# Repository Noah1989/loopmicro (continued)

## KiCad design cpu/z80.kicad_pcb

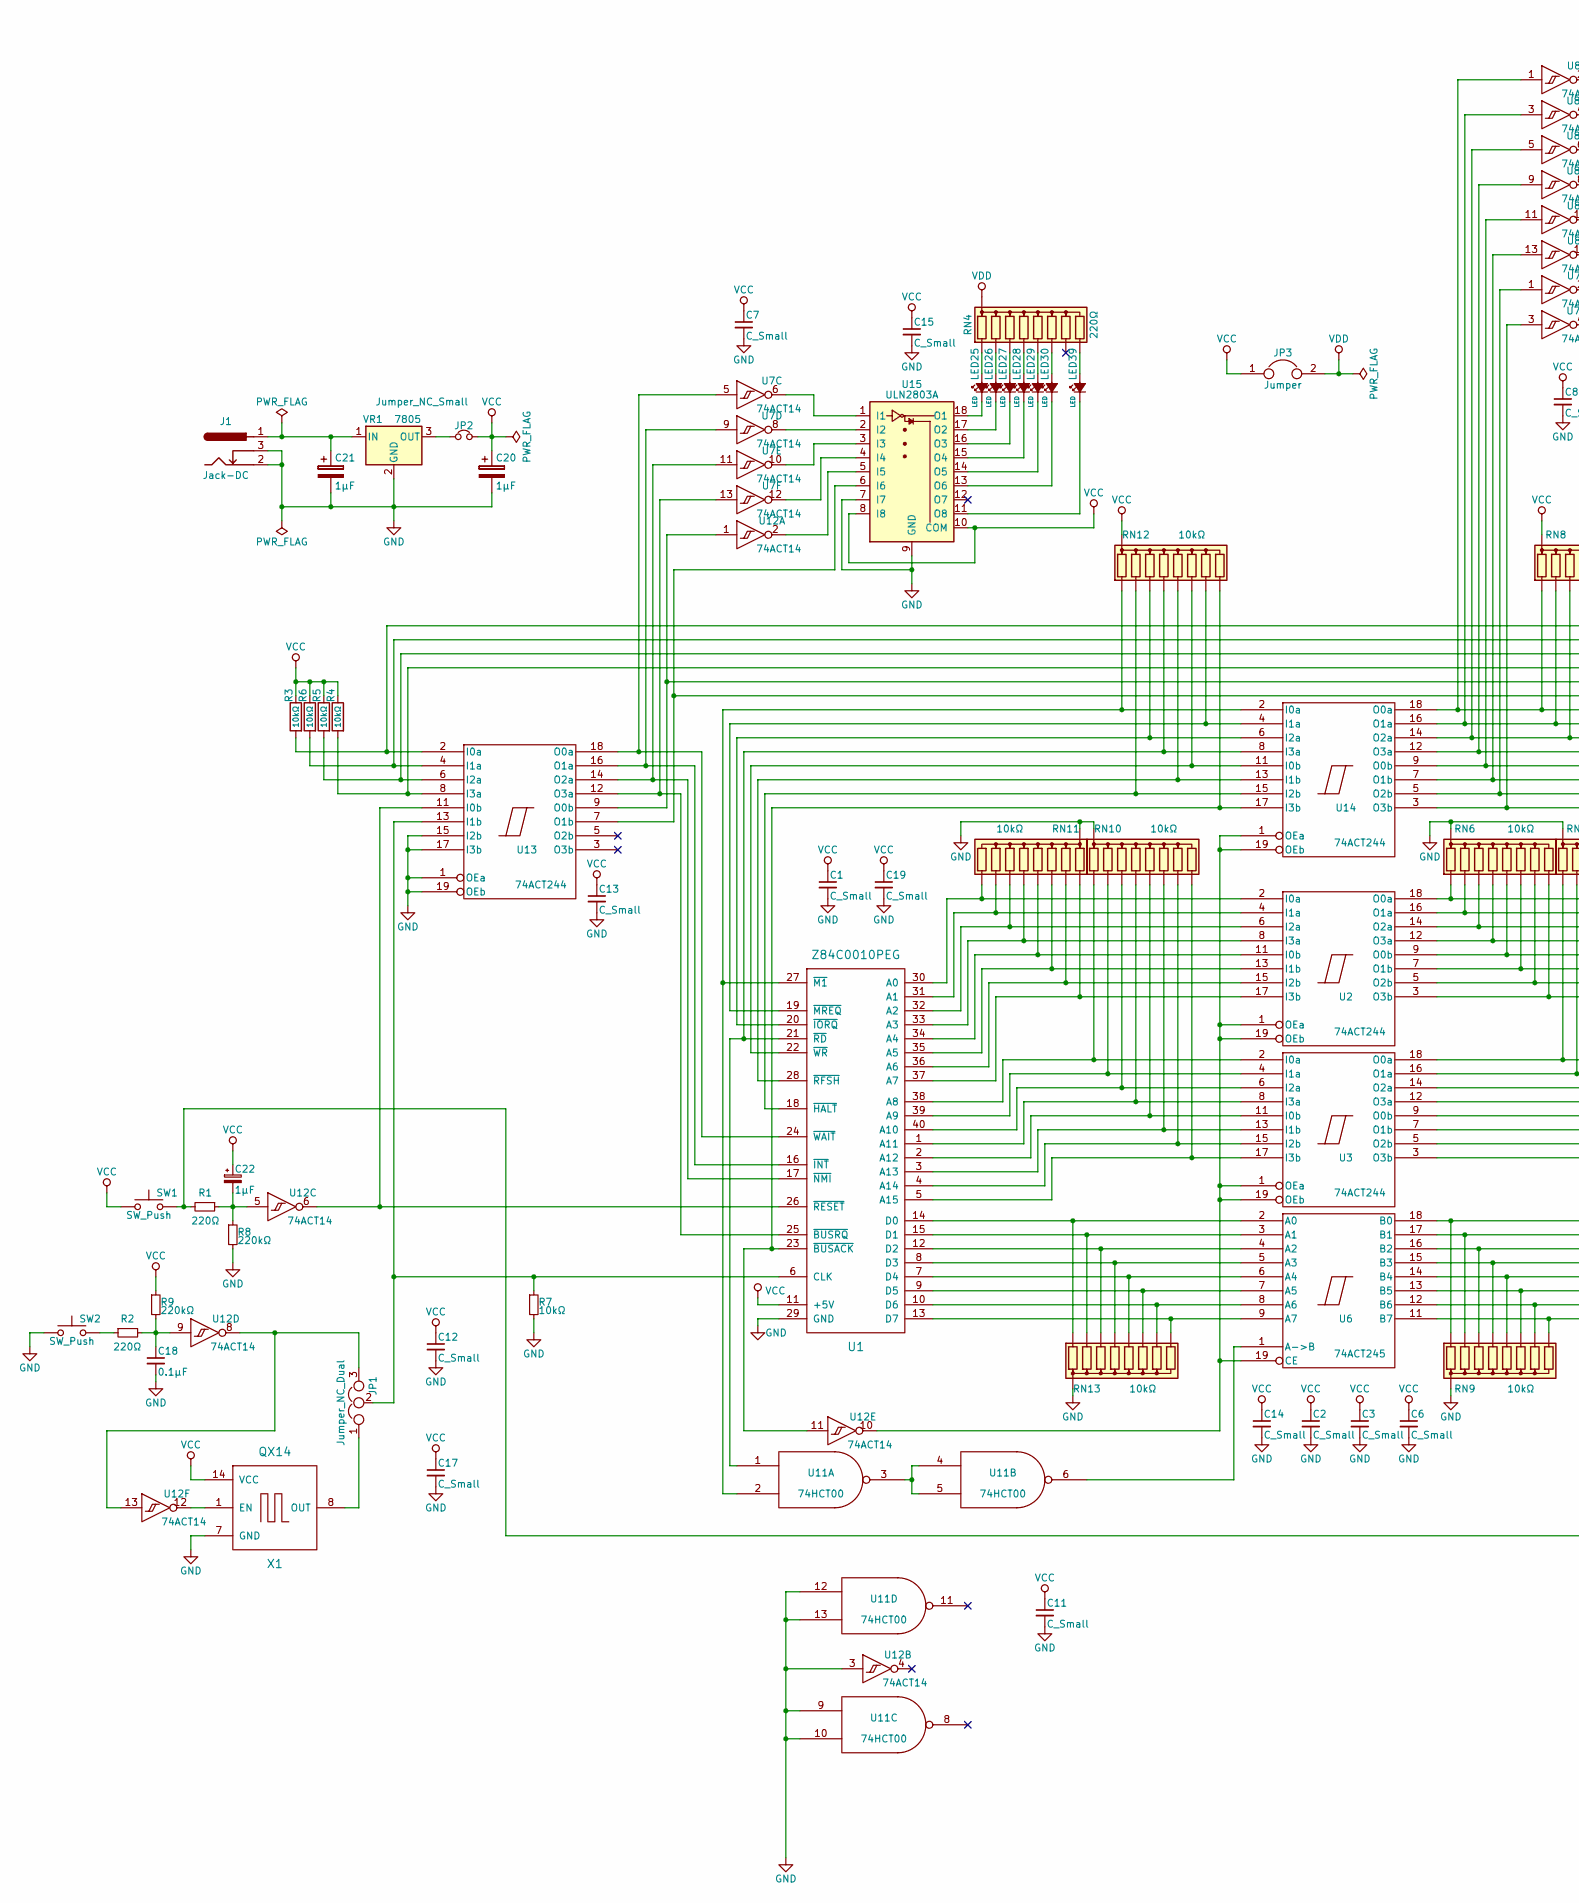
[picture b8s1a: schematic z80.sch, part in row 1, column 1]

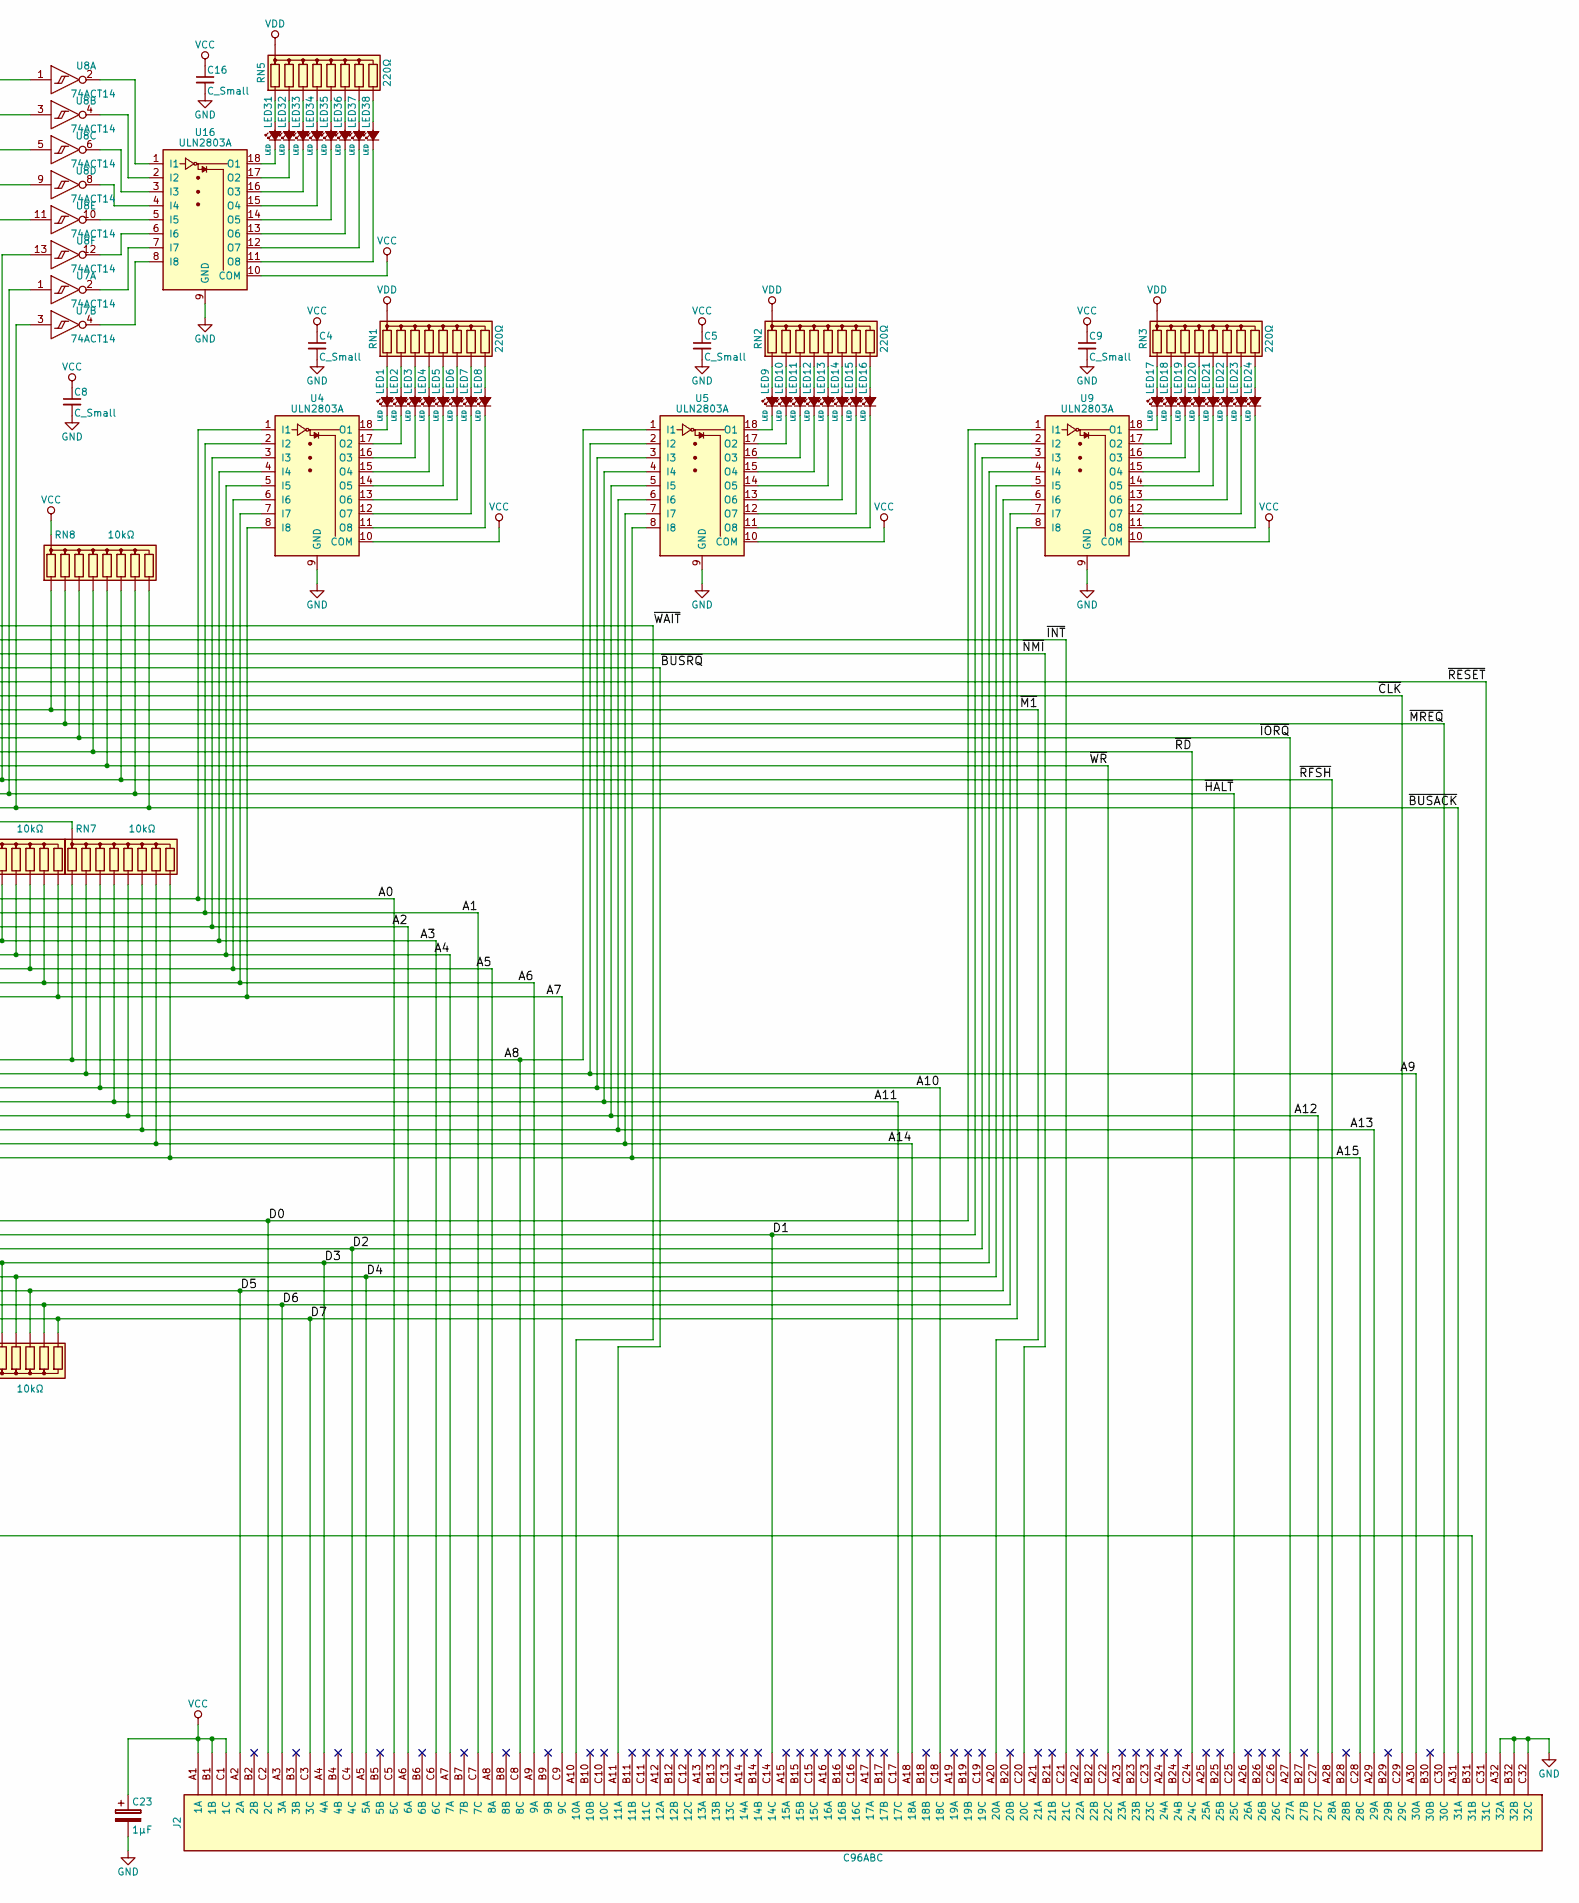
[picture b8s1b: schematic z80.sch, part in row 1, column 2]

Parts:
C1, C2, C3, C4, C5, C6, C7, C8, C9, C11, C12, C13, C14, C15, C16, C17, C19: C_Small; C_Rect_L7.0mm_W3.5mm_P5.00mm
C18: 0.1µF; C_Rect_L7.0mm_W3.5mm_P5.00mm
C20, C21, C22, C23: 1µF; CP_Radial_D5.0mm_P2.00mm
J1: Jack-DC; BARREL_JACK
J2: C96ABC; Socket_DIN41612-CaseC1-full-Male-96Pin-3rows
JP1: Jumper_NC_Dual; Pin_Header_Straight_1x03_Pitch2.54mm
JP2: Jumper_NC_Small; Pin_Header_Straight_2x01_Pitch2.54mm
JP3: Jumper; Pin_Header_Straight_2x01_Pitch2.54mm
LED1, LED2, LED3, LED4, LED5, LED6, LED7, LED8, LED9, LED10, LED11, LED12, LED13, LED14, LED15, LED16, LED17, LED18, LED19, LED20, LED21, LED22, LED23, LED24, LED25, LED26, LED27, LED28, LED29, LED30, LED31, LED32, LED33, LED34, LED35, LED36, LED37, LED38: LED; LED_Rectangular_W5.0mm_H2.0mm
LED39: LED; LED_D5.0mm
R1, R2: 220Ω; R_Axial_DIN0207_L6.3mm_D2.5mm_P10.16mm_Horizontal
R3, R4, R5, R6, R7: 10kΩ; R_Axial_DIN0207_L6.3mm_D2.5mm_P10.16mm_Horizontal
R8, R9: 220kΩ; R_Axial_DIN0207_L6.3mm_D2.5mm_P10.16mm_Horizontal
RN1, RN2, RN3, RN4, RN5: 220Ω; R_Array_SIP9
RN6, RN7, RN8, RN9, RN10, RN11, RN12, RN13: 10kΩ; R_Array_SIP9
SW1, SW2: SW_Push; SW_PUSH_6mm_h5mm
U1: Z84C0010PEG; DIP-40_W15.24mm_LongPads
U2, U3, U13, U14: 74ACT244; DIP-20_W7.62mm_LongPads
U4, U5, U9, U15, U16: ULN2803A; DIP-18_W7.62mm_LongPads
U6: 74ACT245; DIP-20_W7.62mm_LongPads
U7, U8, U12: 74ACT14; DIP-14_W7.62mm_LongPads
U11: 74HCT00; DIP-14_W7.62mm_LongPads
VR1: 7805; TO-220-3_Horizontal
X1: QX14; DIP-14_W7.62mm_Socket_LongPads

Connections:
/A0: J2.C5 (5C), RN6.2 (R1), U2.18 (O0a), U4.1 (I1)
/A1: J2.C7 (7C), RN6.3 (R2), U2.16 (O1a), U4.2 (I2)
/A2: J2.A6 (6A), RN6.4 (R3), U2.14 (O2a), U4.3 (I3)
/A3: J2.C6 (6C), RN6.5 (R4), U2.12 (O3a), U4.4 (I4)
/A4: J2.A7 (7A), RN6.6 (R5), U2.9 (O0b), U4.5 (I5)
/A5: J2.A8 (8A), RN6.7 (R6), U2.7 (O1b), U4.6 (I6)
/A6: J2.A9 (9A), RN6.8 (R7), U2.5 (O2b), U4.7 (I7)
/A7: J2.C9 (9C), RN6.9 (R8), U2.3 (O3b), U4.8 (I8)
/A8: J2.C8 (8C), RN7.2 (R1), U3.18 (O0a), U5.1 (I1)
/A9: J2.A30 (30A), RN7.3 (R2), U3.16 (O1a), U5.2 (I2)
/A10: J2.C18 (18C), RN7.4 (R3), U3.14 (O2a), U5.3 (I3)
/A11: J2.C17 (17C), RN7.5 (R4), U3.12 (O3a), U5.4 (I4)
/A12: J2.C27 (27C), RN7.6 (R5), U3.9 (O0b), U5.5 (I5)
/A13: J2.A29 (29A), RN7.7 (R6), U3.7 (O1b), U5.6 (I6)
/A14: J2.A18 (18A), RN7.8 (R7), U3.5 (O2b), U5.7 (I7)
/A15: J2.C28 (28C), RN7.9 (R8), U3.3 (O3b), U5.8 (I8)
/D0: J2.C2 (2C), RN9.2 (R1), U6.18 (B0), U9.1 (I1)
/D1: J2.C14 (14C), RN9.3 (R2), U6.17 (B1), U9.2 (I2)
/D2: J2.C4 (4C), RN9.4 (R3), U6.16 (B2), U9.3 (I3)
/D3: J2.A4 (4A), RN9.5 (R4), U6.15 (B3), U9.4 (I4)
/D4: J2.A5 (5A), RN9.6 (R5), U6.14 (B4), U9.5 (I5)
/D5: J2.A2 (2A), RN9.7 (R6), U6.13 (B5), U9.6 (I6)
/D6: J2.A3 (3A), RN9.8 (R7), U6.12 (B6), U9.7 (I7)
/D7: J2.C3 (3C), RN9.9 (R8), U6.11 (B7), U9.8 (I8)
/~BUSACK: J2.A31 (31A), RN8.9 (R8), U7.3, U14.3 (O3b)
/~BUSRQ: J2.A11 (11A), R4.2, U13.8 (I3a)
/~CLK: J2.C29 (29C), U13.7 (O1b), U15.6 (I6)
/~HALT: J2.C25 (25C), RN8.8 (R7), U7.1, U14.5 (O2b)
/~INT: J2.C21 (21C), R6.2, U13.4 (I1a)
/~IORQ: J2.A27 (27A), RN8.4 (R3), U8.5, U14.14 (O2a)
/~M1: J2.A20 (20A), RN8.2 (R1), U8.1, U14.18 (O0a)
/~MREQ: J2.C30 (30C), RN8.3 (R2), U8.3, U14.16 (O1a)
/~NMI: J2.C20 (20C), R5.2, U13.6 (I2a)
/~RD: J2.C24 (24C), RN8.5 (R4), U8.9, U14.12 (O3a)
/~RESET: J2.C31 (31C), U12.1, U13.9 (O0b)
/~RFSH: J2.A28 (28A), RN8.7 (R6), U8.13, U14.7 (O1b)
/~WAIT: J2.A10 (10A), R3.2, U13.2 (I0a)
/~WR: J2.C22 (22C), RN8.6 (R5), U8.11, U14.9 (O0b)
GND: C1.2, C2.2, C3.2, C4.2, C5.2, C6.2, C7.2, C8.2, C9.2, C11.2, C12.2, C13.2, C14.2, C15.2, C16.2, C17.2, C18.2, C19.2, C20.2, C21.2, C23.2, J1.2, J1.3, J2.A32 (32A), J2.B32 (32B), J2.C32 (32C), R7.2, R8.2, RN6.1 (common), RN7.1 (common), RN9.1 (common), RN10.1 (common), RN11.1 (common), RN13.1 (common), SW2.1, U1.29 (GND), U2.10 (GND), U3.10 (GND), U4.9 (GND), U5.9 (GND), U6.10 (GND), U7.7 (GND), U8.7 (GND), U9.9 (GND), U11.7 (GND), U11.9, U11.10, U11.12, U11.13, U12.3, U12.7 (GND), U13.1 (OEa), U13.10 (GND), U13.15 (I2b), U13.17 (I3b), U13.19 (OEb), U14.10 (GND), U15.7 (I7), U15.9 (GND), U16.9 (GND), VR1.2 (GND), X1.7 (GND)
unnamed: C18.1, R2.2, R9.2, U12.9
unnamed: C21.1, J1.1, VR1.1 (IN)
unnamed: C22.2, R1.1, R8.1, U12.5
unnamed: J2.B31 (31B), R1.2, SW1.2
unnamed: JP1.1, X1.8 (OUT)
unnamed: JP1.2, R7.1, U1.6 (CLK), U13.13 (I1b)
unnamed: JP1.3, U12.8, U12.13
unnamed: JP2.1, VR1.3 (OUT)
unnamed: LED1.1 (K), U4.18 (O1)
unnamed: LED1.2 (A), RN1.2 (R1)
unnamed: LED2.1 (K), U4.17 (O2)
unnamed: LED2.2 (A), RN1.3 (R2)
unnamed: LED3.1 (K), U4.16 (O3)
unnamed: LED3.2 (A), RN1.4 (R3)
unnamed: LED4.1 (K), U4.15 (O4)
unnamed: LED4.2 (A), RN1.5 (R4)
unnamed: LED5.1 (K), U4.14 (O5)
unnamed: LED5.2 (A), RN1.6 (R5)
unnamed: LED6.1 (K), U4.13 (O6)
unnamed: LED6.2 (A), RN1.7 (R6)
unnamed: LED7.1 (K), U4.12 (O7)
unnamed: LED7.2 (A), RN1.8 (R7)
unnamed: LED8.1 (K), U4.11 (O8)
unnamed: LED8.2 (A), RN1.9 (R8)
unnamed: LED9.1 (K), U5.18 (O1)
unnamed: LED9.2 (A), RN2.2 (R1)
unnamed: LED10.1 (K), U5.17 (O2)
unnamed: LED10.2 (A), RN2.3 (R2)
unnamed: LED11.1 (K), U5.16 (O3)
unnamed: LED11.2 (A), RN2.4 (R3)
unnamed: LED12.1 (K), U5.15 (O4)
unnamed: LED12.2 (A), RN2.5 (R4)
unnamed: LED13.1 (K), U5.14 (O5)
unnamed: LED13.2 (A), RN2.6 (R5)
unnamed: LED14.1 (K), U5.13 (O6)
unnamed: LED14.2 (A), RN2.7 (R6)
unnamed: LED15.1 (K), U5.12 (O7)
unnamed: LED15.2 (A), RN2.8 (R7)
unnamed: LED16.1 (K), U5.11 (O8)
unnamed: LED16.2 (A), RN2.9 (R8)
unnamed: LED17.1 (K), U9.18 (O1)
unnamed: LED17.2 (A), RN3.2 (R1)
unnamed: LED18.1 (K), U9.17 (O2)
unnamed: LED18.2 (A), RN3.3 (R2)
unnamed: LED19.1 (K), U9.16 (O3)
unnamed: LED19.2 (A), RN3.4 (R3)
unnamed: LED20.1 (K), U9.15 (O4)
unnamed: LED20.2 (A), RN3.5 (R4)
unnamed: LED21.1 (K), U9.14 (O5)
unnamed: LED21.2 (A), RN3.6 (R5)
unnamed: LED22.1 (K), U9.13 (O6)
unnamed: LED22.2 (A), RN3.7 (R6)
unnamed: LED23.1 (K), U9.12 (O7)
unnamed: LED23.2 (A), RN3.8 (R7)
unnamed: LED24.1 (K), U9.11 (O8)
unnamed: LED24.2 (A), RN3.9 (R8)
unnamed: LED25.1 (K), U15.18 (O1)
unnamed: LED25.2 (A), RN4.2 (R1)
unnamed: LED26.1 (K), U15.17 (O2)
unnamed: LED26.2 (A), RN4.3 (R2)
unnamed: LED27.1 (K), U15.16 (O3)
unnamed: LED27.2 (A), RN4.4 (R3)
unnamed: LED28.1 (K), U15.15 (O4)
unnamed: LED28.2 (A), RN4.5 (R4)
unnamed: LED29.1 (K), U15.14 (O5)
unnamed: LED29.2 (A), RN4.6 (R5)
unnamed: LED30.1 (K), U15.13 (O6)
unnamed: LED30.2 (A), RN4.7 (R6)
unnamed: LED31.1 (K), U16.18 (O1)
unnamed: LED31.2 (A), RN5.2 (R1)
unnamed: LED32.1 (K), U16.17 (O2)
unnamed: LED32.2 (A), RN5.3 (R2)
unnamed: LED33.1 (K), U16.16 (O3)
unnamed: LED33.2 (A), RN5.4 (R3)
unnamed: LED34.1 (K), U16.15 (O4)
unnamed: LED34.2 (A), RN5.5 (R4)
unnamed: LED35.1 (K), U16.14 (O5)
unnamed: LED35.2 (A), RN5.6 (R5)
unnamed: LED36.1 (K), U16.13 (O6)
unnamed: LED36.2 (A), RN5.7 (R6)
unnamed: LED37.1 (K), U16.12 (O7)
unnamed: LED37.2 (A), RN5.8 (R7)
unnamed: LED38.1 (K), U16.11 (O8)
unnamed: LED38.2 (A), RN5.9 (R8)
unnamed: LED39.1 (K), U15.11 (O8)
unnamed: LED39.2 (A), RN4.9 (R8)
unnamed: R2.1, SW2.2
unnamed: RN10.2 (R1), U1.38 (A8), U3.2 (I0a)
unnamed: RN10.3 (R2), U1.39 (A9), U3.4 (I1a)
unnamed: RN10.4 (R3), U1.40 (A10), U3.6 (I2a)
unnamed: RN10.5 (R4), U1.1 (A11), U3.8 (I3a)
unnamed: RN10.6 (R5), U1.2 (A12), U3.11 (I0b)
unnamed: RN10.7 (R6), U1.3 (A13), U3.13 (I1b)
unnamed: RN10.8 (R7), U1.4 (A14), U3.15 (I2b)
unnamed: RN10.9 (R8), U1.5 (A15), U3.17 (I3b)
unnamed: RN11.2 (R1), U1.37 (A7), U2.17 (I3b)
unnamed: RN11.3 (R2), U1.36 (A6), U2.15 (I2b)
unnamed: RN11.4 (R3), U1.35 (A5), U2.13 (I1b)
unnamed: RN11.5 (R4), U1.34 (A4), U2.11 (I0b)
unnamed: RN11.6 (R5), U1.33 (A3), U2.8 (I3a)
unnamed: RN11.7 (R6), U1.32 (A2), U2.6 (I2a)
unnamed: RN11.8 (R7), U1.31 (A1), U2.4 (I1a)
unnamed: RN11.9 (R8), U1.30 (A0), U2.2 (I0a)
unnamed: RN12.2 (R1), U1.27 (~M1), U11.2, U14.2 (I0a)
unnamed: RN12.3 (R2), U1.18 (~HALT), U14.15 (I2b)
unnamed: RN12.4 (R3), U1.20 (~IORQ), U14.6 (I2a)
unnamed: RN12.5 (R4), U1.21 (~RD), U11.1, U14.8 (I3a)
unnamed: RN12.6 (R5), U1.28 (~RFSH), U14.13 (I1b)
unnamed: RN12.7 (R6), U1.22 (~WR), U14.11 (I0b)
unnamed: RN12.8 (R7), U1.19 (~MREQ), U14.4 (I1a)
unnamed: RN12.9 (R8), U1.23 (~BUSACK), U12.11, U14.17 (I3b)
unnamed: RN13.2 (R1), U1.14 (D0), U6.2 (A0)
unnamed: RN13.3 (R2), U1.15 (D1), U6.3 (A1)
unnamed: RN13.4 (R3), U1.12 (D2), U6.4 (A2)
unnamed: RN13.5 (R4), U1.8 (D3), U6.5 (A3)
unnamed: RN13.6 (R5), U1.7 (D4), U6.6 (A4)
unnamed: RN13.7 (R6), U1.9 (D5), U6.7 (A5)
unnamed: RN13.8 (R7), U1.10 (D6), U6.8 (A6)
unnamed: RN13.9 (R8), U1.13 (D7), U6.9 (A7)
unnamed: U1.16 (~INT), U7.9, U13.16 (O1a)
unnamed: U1.17 (~NMI), U7.11, U13.14 (O2a)
unnamed: U1.24 (~WAIT), U7.5, U13.18 (O0a)
unnamed: U1.25 (~BUSRQ), U7.13, U13.12 (O3a)
unnamed: U1.26 (~RESET), U12.6, U13.11 (I0b)
unnamed: U11.3, U11.4, U11.5
unnamed: U6.1 (A->B), U11.6
unnamed: U12.2, U15.5 (I5)
unnamed: U2.1 (OEa), U2.19 (OEb), U3.1 (OEa), U3.19 (OEb), U6.19 (CE), U12.10, U14.1 (OEa), U14.19 (OEb)
unnamed: U12.12, X1.1 (EN)
unnamed: U7.6, U15.1 (I1)
unnamed: U7.8, U15.2 (I2)
unnamed: U7.10, U15.3 (I3)
unnamed: U7.12, U15.4 (I4)
unnamed: U8.2, U16.1 (I1)
unnamed: U8.4, U16.2 (I2)
unnamed: U8.6, U16.3 (I3)
unnamed: U8.8, U16.4 (I4)
unnamed: U8.10, U16.5 (I5)
unnamed: U8.12, U16.6 (I6)
unnamed: U7.2, U16.7 (I7)
unnamed: U7.4, U16.8 (I8)
VCC: C1.1, C2.1, C3.1, C4.1, C5.1, C6.1, C7.1, C8.1, C9.1, C11.1, C12.1, C13.1, C14.1, C15.1, C16.1, C17.1, C19.1, C20.1, C22.1, C23.1, J2.A1 (1A), J2.B1 (1B), J2.C1 (1C), JP2.2, JP3.1, R3.1, R4.1, R5.1, R6.1, R9.1, RN8.1 (common), RN12.1 (common), SW1.1, U1.11 (+5V), U2.20 (VCC), U3.20 (VCC), U4.10 (COM), U5.10 (COM), U6.20 (VCC), U7.14 (VCC), U8.14 (VCC), U9.10 (COM), U11.14 (VCC), U12.14 (VCC), U13.20 (VCC), U14.20 (VCC), U15.8 (I8), U15.10 (COM), U16.10 (COM), X1.14 (VCC)
VDD: JP3.2, RN1.1 (common), RN2.1 (common), RN3.1 (common), RN4.1 (common), RN5.1 (common)

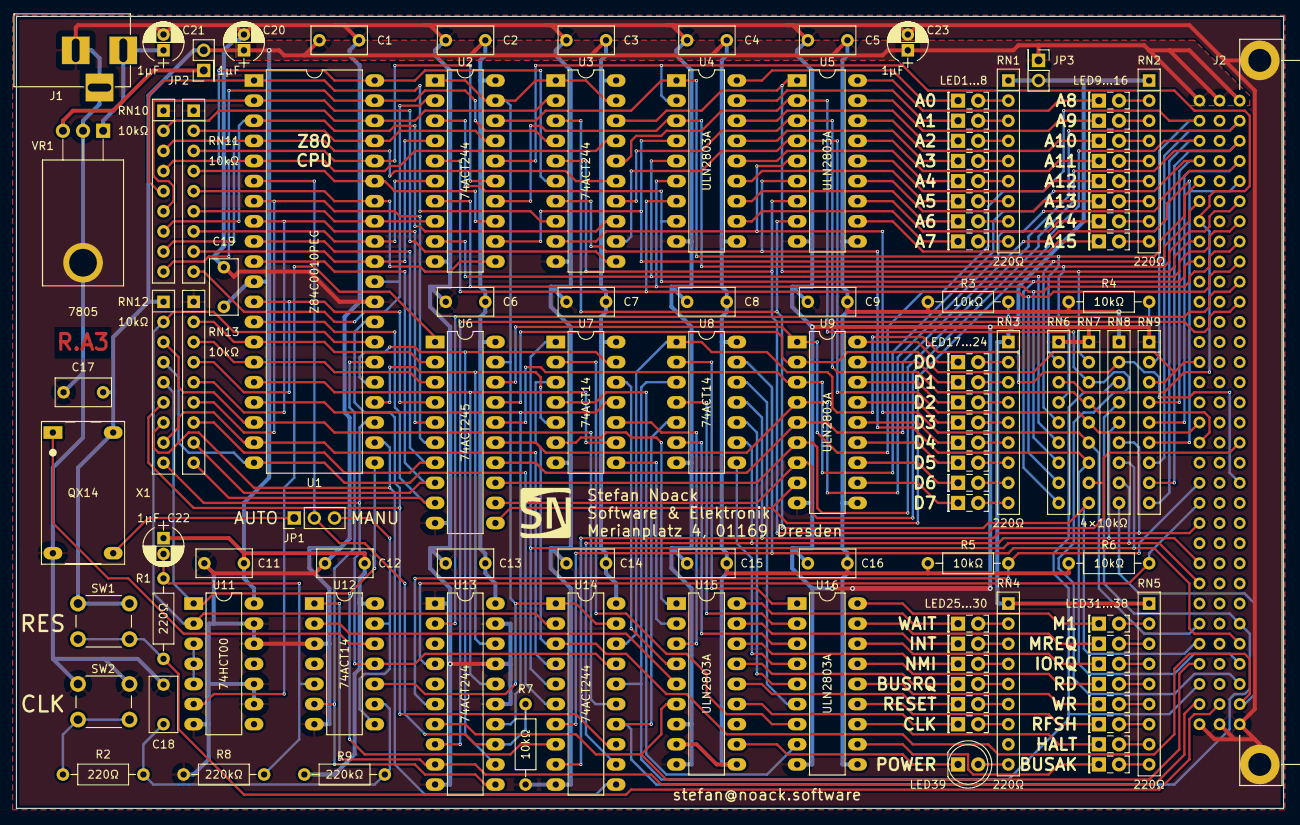
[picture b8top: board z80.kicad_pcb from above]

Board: 2 copper layers, 160.0 x 100.0 mm, 107 parts (0 on the bottom side), 182 nets.

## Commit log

2019-05-15 added memory board schematics
2019-05-15 generated memory board netlist
2019-05-16 add gpu sync generator board
2019-05-18 gpu sync board component placement
2019-05-18 looks like this file is important
2019-05-20 gpu sync board routed
2019-05-20 layout memory
2019-05-25 add ledrom pcb files
2019-05-25 add gpu color pcb
2019-05-25 add cpu pcb
2019-05-25 add monitor pcb
2019-05-25 leave space for guide rails
2019-05-25 gpu color pcb schematic finalized, component placement idea
2019-05-26 component placement
2019-05-27 gpu color pcb routing (wip)
2019-06-02 gpu color pcb routing (almost done)
2019-06-06 gpu color pcb routing
2019-06-10 add 3d shapes
2019-06-10 backplane (wip)
2019-06-10 GPU color: add connector for internal screen; add text and logo
2019-06-15 routed backplane
2019-06-15 add 3d models
2019-06-15 add reset button, minor tweaks
2019-06-16 final pcb layout tweaks / production run
2019-07-25 new cpu board schematic
2019-07-28 new cpu (+ram) board
2019-07-28 routing
2019-08-01 keyboard interface
2019-08-01 minor adjustments
2019-08-02 add sio.lib
2019-09-17 new file
2019-09-20 memory card interface wip
2019-09-26 pcb routing
2020-01-12 add rom (init routines)
2020-01-12 add .gitignore to rom dir
2020-01-13 add machine code monitor
2020-01-16 extract entrypoint symbols from lst file
2020-01-16 minor
2020-02-19 set addr to 0 on clear screen
2020-04-06 use hex format, FF as filler
2020-04-28 store stack pointer on error
2020-04-28 keyboard pcb
2020-08-21 reorganize project
2020-08-22 beginnings of new rom version
2020-08-22 video initialization
2020-08-22 ui elements
2020-08-22 keyboard input
2020-08-25 add work in progress files
2020-08-30 keyboard get_key
2020-08-30 taskbar button input handler
2020-08-30 data segment initializer
2020-08-30 taskbar button toggle behavior
2020-08-30 add help window
2020-08-30 help viewer
2020-08-31 text scrolling
2020-08-31 fix line breaks at full width
2020-10-19 app switching
2020-10-19 memory viewer
2020-11-14 memory viewer info line
2020-11-14 memory viewer cursor movement
2020-11-14 more cursor movement
2020-11-15 cursor page up/down
2020-12-18 memory monitor: editing
2020-12-18 vsync
2020-12-19 bugfixes, sd card init
2020-12-19 implement CMD8
2020-12-19 implement ACMD41
2020-12-19 single block read
2020-12-19 fat32: read volume id
2020-12-20 fat32: read root directory
2020-12-21 list directory contents
2020-12-24 fat32 lfn parsing
2020-12-24 validate lfn sequence numbers, fallback to short file name
2020-12-26 decode some of the ucs-2 characters in filenames, improve short file names
2020-12-27 show / in front of subdirectories
2020-12-27 ui layout
2020-12-31 file browser: layout, cursor, colors
2021-01-01 cursor: limit movement to actual lines
2021-01-01 file browser: navigate directories
2021-01-01 ui design
2021-01-01 file browser: scrolling down
2021-01-01 file browser: scrolling up
2021-01-03 file deletion implemented
2021-01-03 fix cursor on deletion of last file in list
2021-01-09 WIP new file creation
2021-01-10 file name input
2021-01-10 creation of empty files works!
2021-01-24 bugfixes / improvements
2021-02-06 editor: load file, display contents
2021-02-09 color palette experiments
2021-02-13 refactor
2021-03-04 file editor line cursor
2021-03-04 editor: handle edited lines in view (theoretically)
2021-08-02 upgrade collapseos version, wip drivers rewrite
2021-08-04 keyboard driver works now
2021-08-08 implement scrolling
2021-08-08 new CollapseOS release
2021-08-14 sdc driver
2021-08-14 tile modes TM0 and TM1
2021-11-13 emulator: new version using emscipten/c++
2021-11-27 emulator: implement signals
2021-11-28 add labels
2021-11-28 add toggle switch
2021-12-18 Add Z80 CPU
    https://github.com/gdevic/A-Z80 translated to C++ using https://github.com/verilator/verilator
2021-12-18 implement buses
2021-12-20 implement cpu tristate bus interface
2021-12-20 fix svdpi.h
2021-12-21 minor fix
2022-01-17 implement dip switch
2022-01-21 connect cpu signals and add workaround for https://github.com/gdevic/A-Z80/issues/2
2022-01-21 remove useless file
2022-01-22 add front panel connections
2022-01-22 implement memory
2022-01-24 use https://github.com/hutch31/tv80 instead
    verilator does not seem to support circular tristate logic. also, this is much simpler/faster (but less accurate)
2022-01-25 implement persistent memory
2022-01-26 implement LCD
2022-01-27 implement oscillator + LED POV effect
2022-02-02 implement keyboard/sio
2022-04-10 visual tweaks
2022-05-10 add JS bindings to emulator
2022-05-10 add html ui elements
2022-07-05 experimental code
